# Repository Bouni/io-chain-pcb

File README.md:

# io-chain-pcb

A PCB that can be daisy chained to route IO signals on our mill from axis to axis and finally into the cabinet

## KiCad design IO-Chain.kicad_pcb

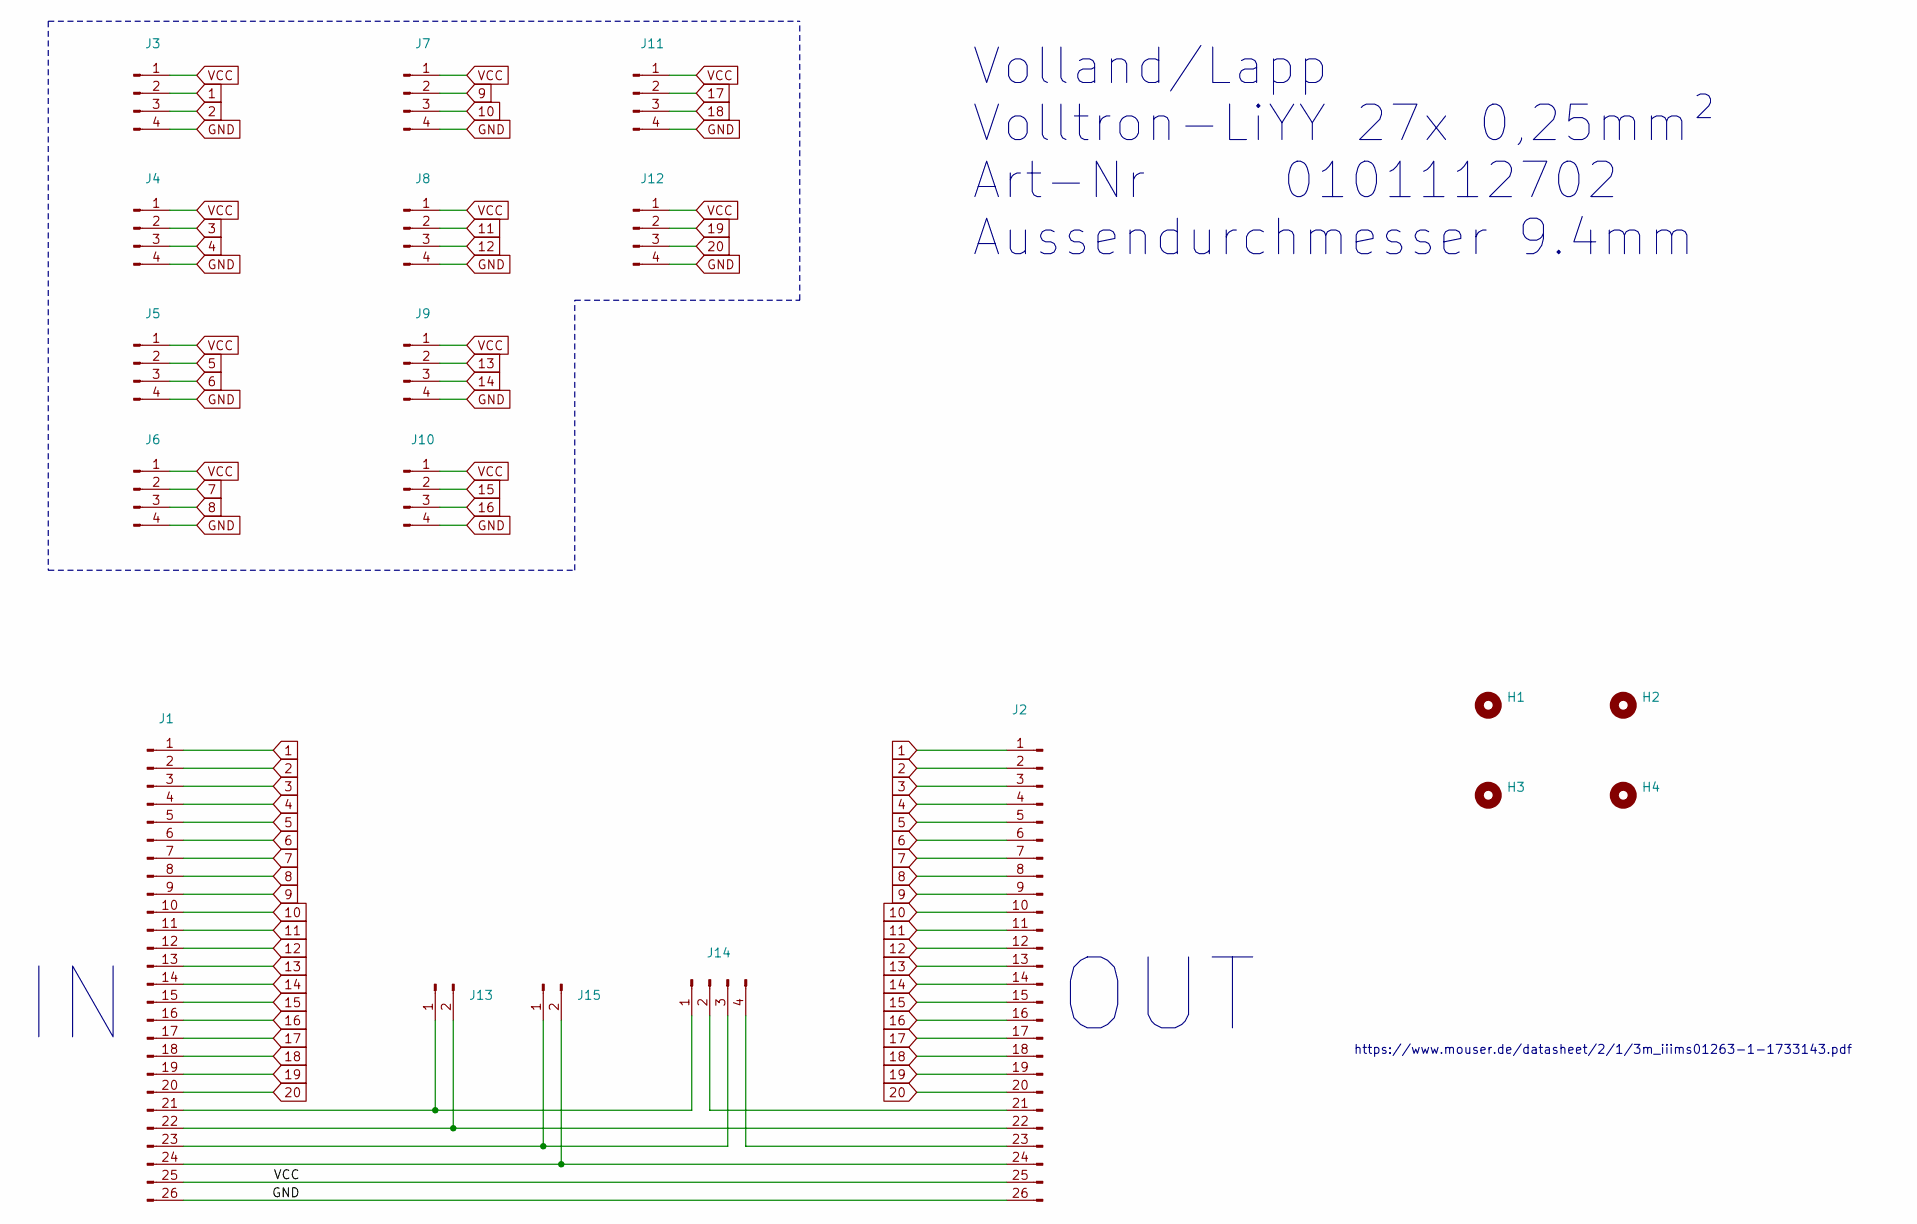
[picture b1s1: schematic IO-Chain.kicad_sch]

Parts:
H1, H2, H3, H4: MountingHole; MountingHole_3.2mm_M3
J1, J2: Conn_01x26_Male; 10250-6212PL
J3, J4, J5, J6, J7, J8, J9, J10, J11, J12, J14: Conn_01x04_Male; PhoenixContact_MCV_1,5_4-G-3.5_1x04_P3.50mm_Vertical
J13, J15: Conn_01x02_Male; PinHeader_1x02_P2.54mm_Vertical

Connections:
1: J1.1, J2.1, J3.2
2: J1.2, J2.2, J3.3
3: J1.3, J2.3, J4.2
4: J1.4, J2.4, J4.3
5: J1.5, J2.5, J5.2
6: J1.6, J2.6, J5.3
7: J1.7, J2.7, J6.2
8: J1.8, J2.8, J6.3
9: J1.9, J2.9, J7.2
10: J1.10, J2.10, J7.3
11: J1.11, J2.11, J8.2
12: J1.12, J2.12, J8.3
13: J1.13, J2.13, J9.2
14: J1.14, J2.14, J9.3
15: J1.15, J2.15, J10.2
16: J1.16, J2.16, J10.3
17: J1.17, J2.17, J11.2
18: J1.18, J2.18, J11.3
19: J1.19, J2.19, J12.2
20: J1.20, J2.20, J12.3
GND: J1.26, J2.26, J3.4, J4.4, J5.4, J6.4, J7.4, J8.4, J9.4, J10.4, J11.4, J12.4
unnamed: J1.21, J13.1, J14.1
unnamed: J1.22, J2.22, J13.2
unnamed: J1.23, J14.3, J15.1
unnamed: J1.24, J2.24, J15.2
unnamed: J2.21, J14.2
unnamed: J2.23, J14.4
VCC: J1.25, J2.25, J3.1, J4.1, J5.1, J6.1, J7.1, J8.1, J9.1, J10.1, J11.1, J12.1

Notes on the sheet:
Volland/Lapp Volltron-LiYY 27x 0,25mm² Art-Nr 0101112702 Aussendurchmesser 9.4mm
OUT
https://www.mouser.de/datasheet/2/1/3m_iiims01263-1-1733143.pdf

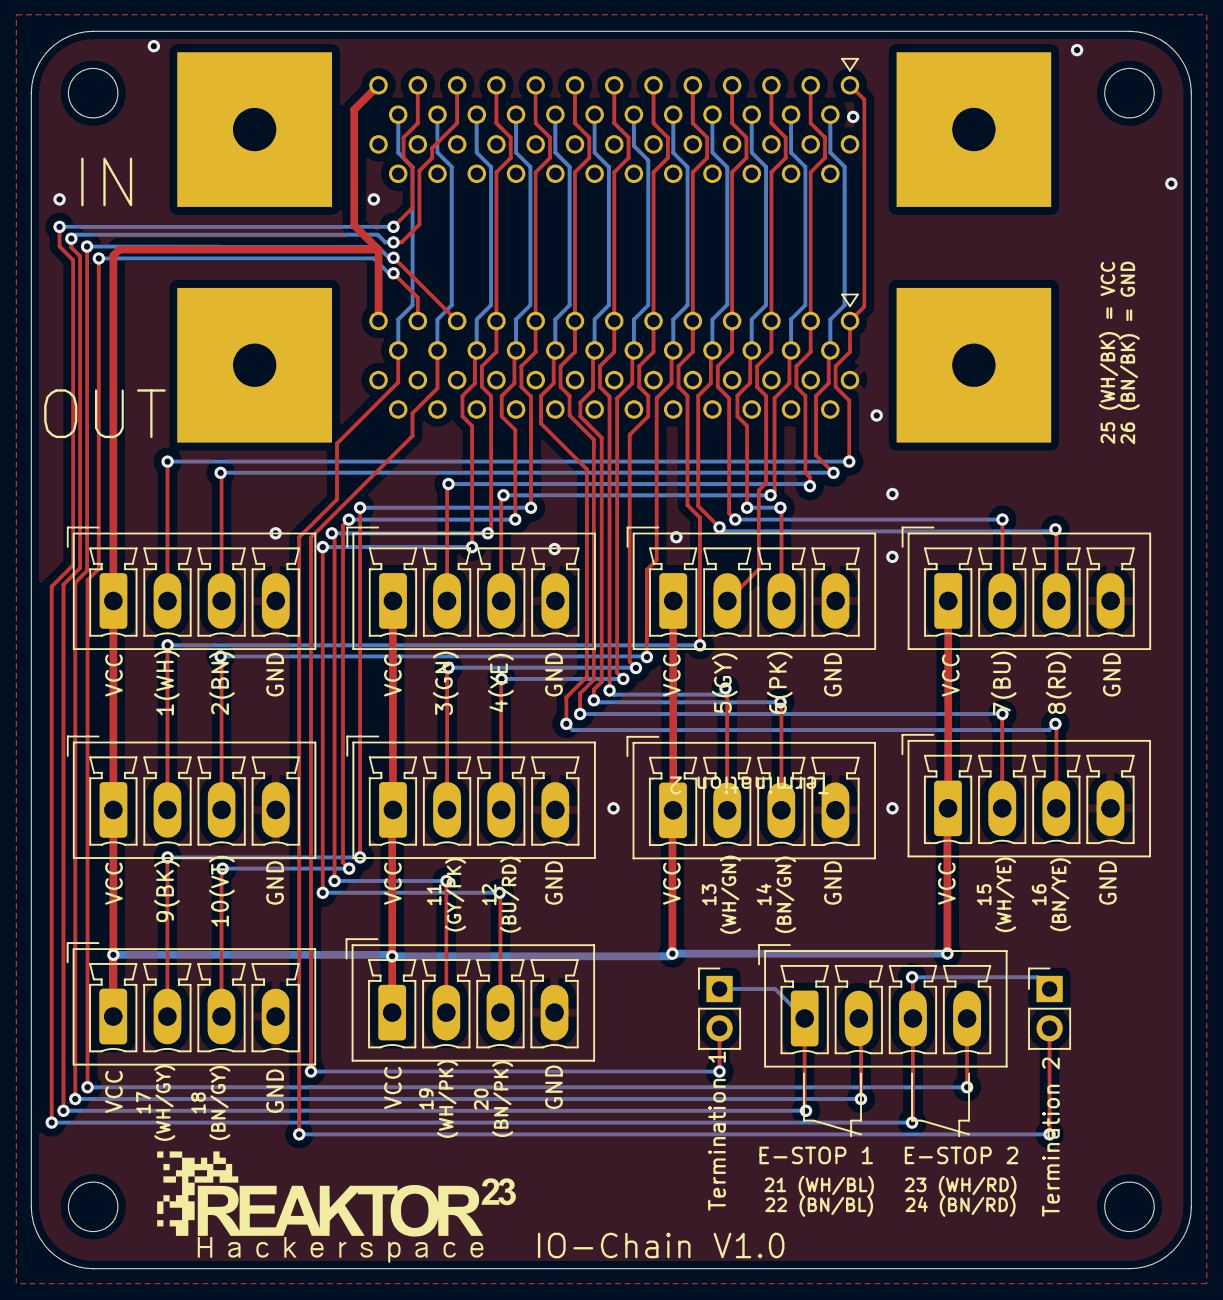
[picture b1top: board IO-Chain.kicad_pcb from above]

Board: 2 copper layers, 75.0 x 80.0 mm, 19 parts (0 on the bottom side), 28 nets.
